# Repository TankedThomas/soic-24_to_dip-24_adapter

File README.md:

# SOIC-24 to DIP-24 Adapter
## Currently untested - this line will be removed once I have a chance to test it
This is basic adapter PCB for using SOIC-24 chips (SMD) as DIP-24 chips (through-hole), made in KiCad.

The adapter is designed to be more or less the same size as a regular DIP-24 IC.

It's especially useful for ICs available in an SOIC-24 package but no longer in a DIP-24 package, such as modern 6116 RAM chips.

There is no decoupling capacitor on the board as it's expected that the main board will already have them.

## Fabrication
Gerber files are provided. Default settings (2 layers, etc.) on fabrication websites such as JLCPCB and PCBWay should suffice.

Map files and pick-and-place files are also included.

## Building
2x 1x12 male header pins are required, plus an SOIC-24 IC of your choice.

It is recommended to solder the SOIC-24 first, as soldering the header pins first will give less clearance for the IC, especially when using a soldering iron.

## Legal
This project's copyright is owned by Gare Ltd., and uses the CERN Open Hardware Licence Version 2 (Strongly Reciprocal).

Complete sources of licensed works and modifications must be made public, notices and license must be preserved, and contributors provide an express grant of patent rights.

No warranty is provided for this project. Responsibility for using this product legally and safely is up to the end user.

&copy; Gare Ltd.

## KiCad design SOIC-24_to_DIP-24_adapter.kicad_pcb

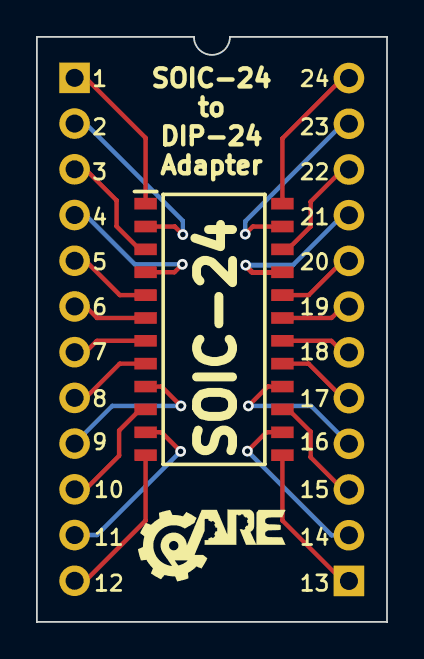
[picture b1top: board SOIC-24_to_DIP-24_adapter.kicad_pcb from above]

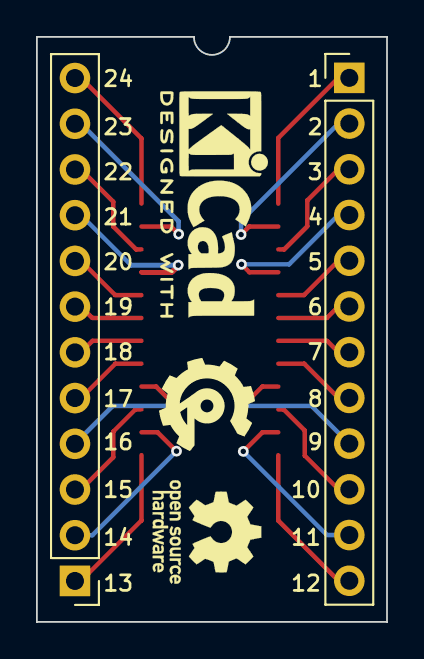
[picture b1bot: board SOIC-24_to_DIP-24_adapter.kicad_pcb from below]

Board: 2 copper layers, 19.4 x 32.5 mm, 7 parts (5 on the bottom side), 24 nets.

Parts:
Gare_Cog: LOGO; Gare Cog
Gare_Logo: LOGO; Gare Logo
J1, J2: Conn_01x12_Pin; PinHeader_1x12_P2.54mm_Vertical
KiCad: KiCad-Logo2_5mm_SilkScreen
OSHW: OSHW-Logo_5.7x6mm_SilkScreen
SOIC-24: 6116; SOIC127P786X210-24N

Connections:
GND: J1.12, SOIC-24.12 (GND)
unnamed: J1.8, SOIC-24.8 (A0)
unnamed: J1.7, SOIC-24.7 (A1)
unnamed: J1.6, SOIC-24.6 (A2)
unnamed: J1.5, SOIC-24.5 (A3)
unnamed: J1.4, SOIC-24.4 (A4)
unnamed: J1.3, SOIC-24.3 (A5)
unnamed: J1.2, SOIC-24.2 (A6)
unnamed: J1.1, SOIC-24.1 (A7)
unnamed: J2.11, SOIC-24.23 (A8)
unnamed: J2.10, SOIC-24.22 (A9)
unnamed: J2.7, SOIC-24.19 (A10)
unnamed: J1.9, SOIC-24.9 (I/O_0)
unnamed: J1.10, SOIC-24.10 (I/O_1)
unnamed: J1.11, SOIC-24.11 (I/O_2)
unnamed: J2.1, SOIC-24.13 (I/O_3)
unnamed: J2.2, SOIC-24.14 (I/O_4)
unnamed: J2.3, SOIC-24.15 (I/O_5)
unnamed: J2.4, SOIC-24.16 (I/O_6)
unnamed: J2.5, SOIC-24.17 (I/O_7)
unnamed: J2.6, SOIC-24.18 (~CS)
unnamed: J2.8, SOIC-24.20 (~OE)
unnamed: J2.9, SOIC-24.21 (~WE)
VCC: J2.12, SOIC-24.24 (VCC)

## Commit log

2025-03-05 Add CAD image
